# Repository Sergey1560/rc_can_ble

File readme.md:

# RaceChrono BLE CAN и GPS адаптер

[English version](./readme_en.md)

GPS приемник и CAN адаптер для работы с [RaceChrono](https://racechrono.com/) через BLE ([подробности протокола](https://github.com/aollin/racechrono-ble-diy-device)). 

В качестве управляющего МК использован NRF52840. Для упрощения сборки используется готовый модуль [Ebyte E73-2G4M08S1C](https://aliexpress.ru/item/1005004834868792.html) ([datasheet](./doc/S1C_Usermanual_v1.9.pdf))

В качестве GPS приемника используется [Ublox M9N](https://www.u-blox.com/en/product/neo-m9n-module) с частотой обновления 25Hz.

CAN реализован на [MCP2515](./doc/MCP2515-Stand-Alone-CAN-Controller-with-SPI-20001801J.pdf) и транссивере SN65HVD230. Для упрощения покупки mcp2515 снята с [готового модуля](https://aliexpress.ru/item/32817132818.html), с которого так же был снят кварц и конденсаторы кварца.

[Схема](./shematic/nrf52840_dev.pdf)

Проект выполнен в Kicad 7.

## Список компонентов

Интерактивный BOM находится в bom/ibom.html

| Элемент     | Количество | Номинал | Посадочное место | Описание
| ----------- | ----------- | ----------- | ----------- | -----------
|C1, C18, C19|3|1uF|Capacitor_SMD:C_0805_2012Metric| |
|C2, C12     |2|10uF|Capacitor_SMD:C_0805_2012Metric| | 
|C3, C4      |2|C_Small|Capacitor_SMD:C_0603_1608Metric|Сняты с модуля CAN|
|C5, C6, C13, C14, C49|5|0.1uF|Capacitor_SMD:C_0805_2012Metric| |
|C7|1|1F|Capacitor_THT:CP_Radial D8.0mm_P3.50mm|Используется как источник резервного питания GPS модуля|
|C11, C20, C40|3|0.01uF|Capacitor_SMD:C_0603_1608Metric| |
|C15|1|1.6pF|Capacitor_SMD:C_0402_1005Metric| |
|C16, C17|2|47uF|Capacitor_Tantalum SMD:CP_EIA-7343-31_Kemet-D| |
|D1, D2|  2|LED_Small|LED_SMD:LED_1206_3216Metric| |
|D3    |1|NUP2105L|Package_TO_SOT_SMD:SOT-23|Dual Line CAN Bus Protector, 24Vrwm|
|D4    |1|1N4148|Diode_SMD:D_SOD-323| |
|D18   |1|BZT52C16S|Diode_SMD:D_SOD-323| |
|D19   |1|STPS2L25|Diode_SMD:D_SMB"| |
|J1|1|Conn 01x04|JST_XH_S4B-XH-A-1_1x04_P2.50mm_Horizontal| |
|J2|1|Coaxial Power|SMA_Amphenol_901-144_Vertical| |
|J3|1|SWD|PinHeader_2x05_P1.27mm_Vertical_SMD| |
|L1|1|8.2uH|power:Inductor8.2| |
|L2|1|27nH|Inductor_SMD:L_0805_2012| |
|Q5|1|AO3401A|Package_TO_SOT_SMD:SOT-23| |
|R1, R2|2|1K|Resistor_SMD:R_0805_2012Metric| |
|R3|1|120|Resistor_SMD:R_0603_1608Metric| |
|R4|1|100|Resistor_SMD:R_0805_2012Metric| |
|R27|1|10K|Resistor_SMD:R_0603_1608Metric| |
|R28|1|187K|Resistor_SMD:R_0603_1608Metric| |
|R29|1|60.4K|Resistor_SMD:R_0603_1608Metric| |
|R40|1|10|Resistor_SMD:R_1206_3216Metric| |
|U1|1|E73-2G4M08S1C|E73-2G4M08S1C-52840| |
|U2|1|MCP2515-xSO|Package_SO:SOIC-18W|Stand-Alone CAN Controller with SPI Interface<br>Снят с модуля CAN|
|U3|1|ST1S14PHR_MY|Package_SO:SOIC-8-1EP| |
|U4|1|NCP3335|Package_SO:OnSemi_Micro8| |
|U5|1|SN65HVD230|Package_SO:SOIC-8|CAN Bus Transceivers, 3.3V, 1Mbps, Low-Power capabilities|
|U17|1|NEO-9M|ublox:NEO-M8N|Ublox M9N|
|Y1|1|8Mhz|Crystal:Crystal_HC49-4H_Vertical|Снят с модуля CAN|

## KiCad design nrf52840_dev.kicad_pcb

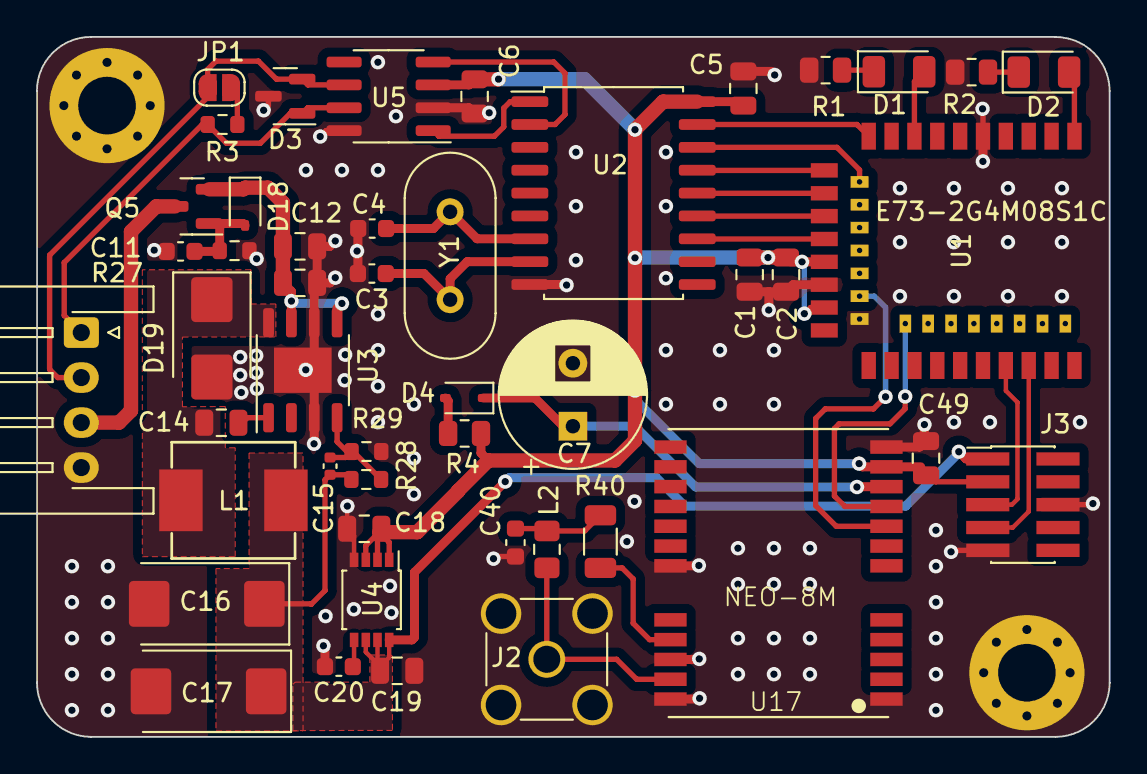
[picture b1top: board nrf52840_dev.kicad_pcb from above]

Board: 2 copper layers, 59.6 x 38.9 mm, 50 parts (1 on the bottom side), 36 nets.

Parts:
C1, C18, C19: 1uF; C_0805_2012Metric
C2, C12: 10uF; C_0805_2012Metric
C3, C4: C_Small; C_0603_1608Metric
C5, C6, C13, C14, C49: 0.1uF; C_0805_2012Metric
C7: 1F; CP_Radial_D8.0mm_P3.50mm
C11, C20, C40: 0.01uF; C_0603_1608Metric
C15: 1.6pF; C_0402_1005Metric
C16, C17: 47uF; CP_EIA-7343-31_Kemet-D_Pad2.25x2.55mm_HandSolder
D1, D2: LED_Small; LED_1206_3216Metric
D3: NUP2105L; SOT-23
D4: 1N4148; D_SOD-323
D18: BZT52C16S; D_SOD-323
D19: STPS2L25; D_SMB
H1, H2: MountingHole_Pad; MountingHole_3.2mm_M3_Pad_Via
J1: Conn_01x04; JST_XH_S4B-XH-A-1_1x04_P2.50mm_Horizontal
J2: Conn_Coaxial_Power; SMA_Amphenol_901-144_Vertical
J3: SWD; PinHeader_2x05_P1.27mm_Vertical_SMD
JP1: terminator; SolderJumper-2_P1.3mm_Open_RoundedPad1.0x1.5mm
L1: 8.2uH; Inductor8.2
L2: 27nH; L_0805_2012Metric_Pad1.15x1.40mm_HandSolder
LOGO1: logo_15x9
Q5: AO3401A; SOT-23
R1, R2: 1K; R_0805_2012Metric
R3: 120; R_0603_1608Metric
R4: 100; R_0805_2012Metric
R27: 10K; R_0603_1608Metric
R28: 187K; R_0603_1608Metric
R29: 60.4K; R_0603_1608Metric
R40: 10; R_1206_3216Metric
U1: E73-2G4M08S1C-52840
U2: MCP2515-xSO; SOIC-18W_7.5x11.6mm_P1.27mm
U3: ST1S14PHR_MY; SOIC-8-1EP_3.9x4.9mm_P1.27mm_EP2.514x3.2mm
U4: NCP3335; OnSemi_Micro8
U5: SN65HVD230; SOIC-8_3.9x4.9mm_P1.27mm
U17: NEO-8M; NEO-M8N
Y1: 8Mhz; Crystal_HC49-4H_Vertical

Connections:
/3V3: C1.1, C2.1, C5.1, C6.1, C18.1, C49.1, J3.3, R4.1, U1.19 (VDD), U1.23 (VDDH), U2.18 (VDD), U4.1 (Vout), U4.2 (Vout), U4.3 (Sense), U5.3 (VCC), U17.23 (VCC)
/5V: C15.1, C16.1, C17.1, C19.1, J3.1, L1.2, R28.1, U4.6 (SD), U4.7 (Vin), U4.8 (Vin)
/12VIN: J1.3, Q5.3 (D)
/CANH: D3.1 (K), J1.1, R3.1, U5.7 (CANH)
/CANL: D3.2 (K), J1.2, JP1.2 (B), U5.6 (CANL)
/CS: U1.12 (P0.26), U2.16 (~CS)
/IRQ: U1.17 (P1.09), U2.12 (~INT)
/LED1: D1.2 (A), U1.8 (P0.29(AIN5))
/LED2: D2.2 (A), U1.1 (P1.11)
/MCP_RST: U1.10 (P0.30(AIN6)), U2.17 (~RESET)
/MISO: U1.11 (P0.00(XL1)), U2.15 (SO)
/MOSI: U1.13 (P0.01(XL2)), U2.14 (SI)
/RX: U1.22 (P0.07), U17.20 (TXD/SPIMISO)
/SCK: U1.15 (P0.05(AIN3)), U2.13 (SCK)
/SWD_CLK: J3.7, U1.39 (SWD_CLK)
/SWD_IO: J3.5, U1.37 (SWDIO)
/TX: U1.28 (P0.15), U17.21 (RXD/SPIMOSI)
/ublox/GPS_RF: J2.1 (In), L2.1, U17.11 (RF_IN)
/ublox/GPS_VBAT: C7.1, D4.1 (K), U17.22 (V_BCKP)
GND: C1.2, C2.2, C3.2, C4.2, C5.2, C6.2, C7.2, C11.2, C12.2, C13.2, C16.2, C17.2, C18.2, C19.2, C20.2, C40.2, C49.2, D3.3 (A), D19.2 (A), H1.1, H2.1, J1.4, J2.2 (Ext), J3.6, J3.9, R1.2, R2.2, R27.2, R29.2, U1.5 (GND), U1.21 (GND), U1.24 (GND), U2.9 (VSS), U3.3 (EN1), U3.6 (GND), U3.9 (PGND), U4.4 (GND), U5.2 (GND), U5.8 (Rs), U17.7 (VDD_USB), U17.10 (GND@1), U17.12 (GND@2), U17.13 (GND@3), U17.24 (GND@4)
unnamed: C40.1, L2.2, R40.1
unnamed: D1.1 (K), R1.1
unnamed: D2.1 (K), R2.1
unnamed: D4.2 (A), R4.2
unnamed: C11.1, D18.2 (A), Q5.1 (G), R27.1
unnamed: C12.1, C13.1, D18.1 (K), Q5.2 (S), U3.5 (En2), U3.7 (Vin)
unnamed: C14.2, D19.1 (K), L1.1, U3.8 (SW)
unnamed: JP1.1 (A), R3.2
unnamed: C3.1, U2.8 (OSC1), Y1.1
unnamed: C4.1, U2.7 (OSC2), Y1.2
unnamed: U2.2 (RXCAN), U5.4 (R)
unnamed: U2.1 (TXCAN), U5.1 (D)
unnamed: C14.1, U3.1 (Boot)
unnamed: C15.2, R28.2, R29.1, U3.4 (FB)
unnamed: C20.1, U4.5 (NR)
unnamed: R40.2, U17.9 (VCC_RF)

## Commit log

2023-06-28 CNC test board
2023-07-21 Small fix
2023-07-25 fixes
2023-07-25 readme
2023-07-25 Update production files, add schematic
2023-07-25 add doc
2023-07-25 BOM layout
2023-08-28 fix readme
